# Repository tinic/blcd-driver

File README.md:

# bldc-driver
Motor driver for brushless dc air conditioner motors

This is a PCB design for readily available adjustable brushless motors used in air conditioning units. These units are great since they are sealed and have ajustable speed while using very little power. I used them to drive a stirrer motor to replace the misspecced AC motors (model YYS6-2/110V/60Hz/0.15A) on the otherwise amazing KOMOS KRYO Inline Draft Beer Chillers which tend to fail quickly and generate extreme amounts of heat (~158F/70C measured). Power consumption is reduced from ~17W to around ~4W for my application while staying _completely_ cool. Torque is ecxellent but not exessive in case of obstructions.

The following units have been tested:

140VDC rated (on 120VAC power):
- ZKFP-20-8-113

310VDC rated (on 240VAC power):
- WZDK30-38G

Notes:
- While these units are rated 140/310VDC they work fine with regular rectified AC power (170/338VDC) which makes the implementation simple/cheap.
- The parts used here are complete overkill as this is not designed for mass manufacturing and the price difference with cheaper parts was negligible in single digit units (~$20 with the DigiKey BOM).
- The only special part here is the 15V DC/DC converter as using a couple of LDOs for this application would have caused excessive power use and heat. A constant current source like a capacitive dropper would not have worked either as the power consumption by these motors on the 15V rail is not constant.
- The PCB was designed to stay under 100x100mm to take advantage of flat price of $5 PCBWay offers for these sizes.

New motor installed in the beer chiller:

New stirrer motor with 3d printed blade on the left, old one on the right:

The push in fittings were completely cooked by the old motor:

Full assembly of the new motor in the chiller, the new PCB is on the bottom right:

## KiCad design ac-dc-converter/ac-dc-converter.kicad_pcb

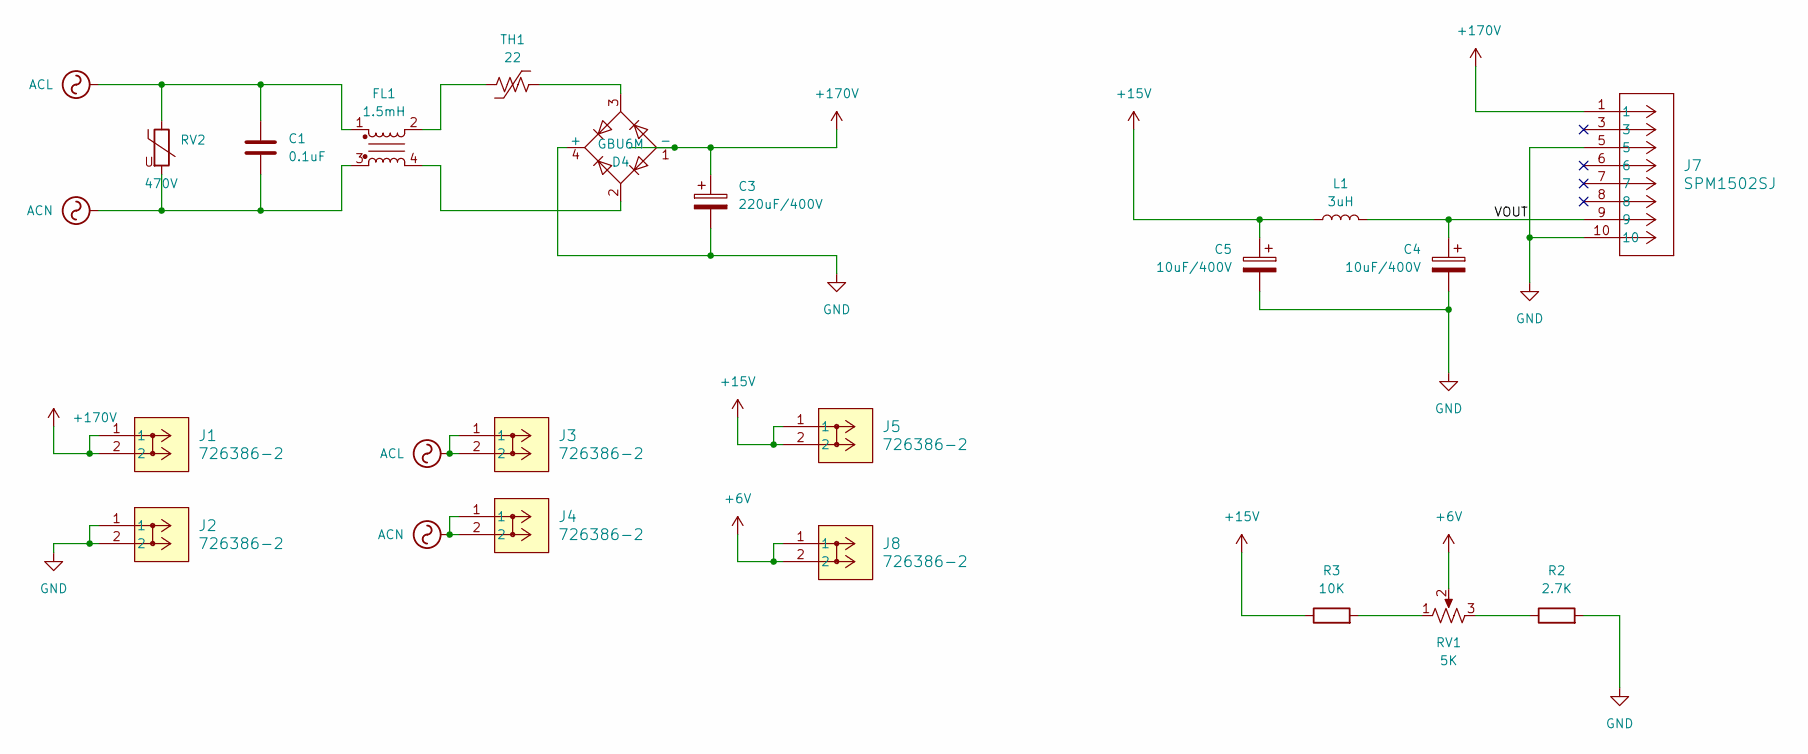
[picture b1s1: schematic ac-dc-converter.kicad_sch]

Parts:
C1: 0.1uF; CAP_17.5 X 10 X 16.5_VIS; Part BFC233810104
C3: 220uF/400V; CP_Radial_D22.0mm_P10.00mm_SnapIn; Part EKMM401VSN221MP50S
C4, C5: 10uF/400V; CP_Radial_D8.0mm_P3.50mm; Part 400AX10MEFC8X16
D4: GBU6M; RECT_GBU_VIS; Part GBU6M
FL1: 1.5mH; SU9HF07015; Part SU9HF-07015
J1, J2, J3, J4, J5, J8: 726386-2; CONN_726386-2_TEC; Part 726386-2
J7: SPM1502SJ; CONN8_502SJ_TMA; Part SPM1502SJ
L1: 3uH; L_Radial_D6.0mm_P4.00mm; Part DRC-V-3R3M
R2: 2.7K; R_Axial_DIN0207_L6.3mm_D2.5mm_P7.62mm_Horizontal; Part RNMF14FTC2K70
R3: 10K; R_Axial_DIN0207_L6.3mm_D2.5mm_P7.62mm_Horizontal; Part MFR-25FRF52-10K
RV1: 5K; Potentiometer_Bourns_3296W_Vertical; Part 3296W-1-502LF
RV2: 470V; VAR_MOV-10D471K_BRN; Part MOV-10D471K
TH1: 22; MF72-010D9_CTM; Part MF72-022D7

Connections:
+6V: J8.1, J8.2, RV1.2
+15V: C5.1, J5.1, J5.2, L1.2, R3.1
+170V: C3.1, D4.1 (-), J1.1, J1.2, J7.1
/VOUT: C4.1, J7.9, L1.1
ACL: C1.1, FL1.1, J3.1, J3.2, RV2.1
ACN: C1.2, FL1.3, J4.1, J4.2, RV2.2
GND: C3.2, C4.2, C5.2, D4.4 (+), J2.1, J2.2, J7.5, J7.10, R2.2
unnamed: D4.2, FL1.4
unnamed: D4.3, TH1.2
unnamed: FL1.2, TH1.1
unnamed: R2.1, RV1.3
unnamed: R3.2, RV1.1

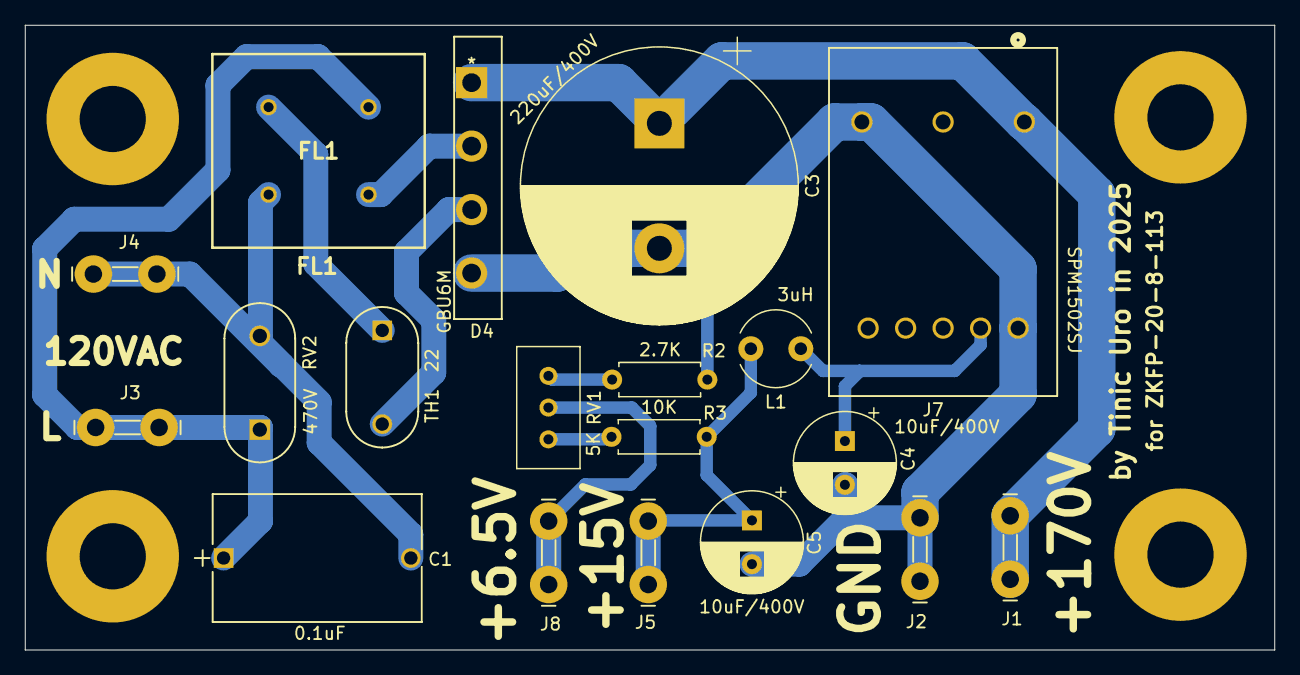
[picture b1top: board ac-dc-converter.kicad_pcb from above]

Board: 2 copper layers, 100.0 x 50.0 mm, 19 parts (0 on the bottom side), 12 nets.
